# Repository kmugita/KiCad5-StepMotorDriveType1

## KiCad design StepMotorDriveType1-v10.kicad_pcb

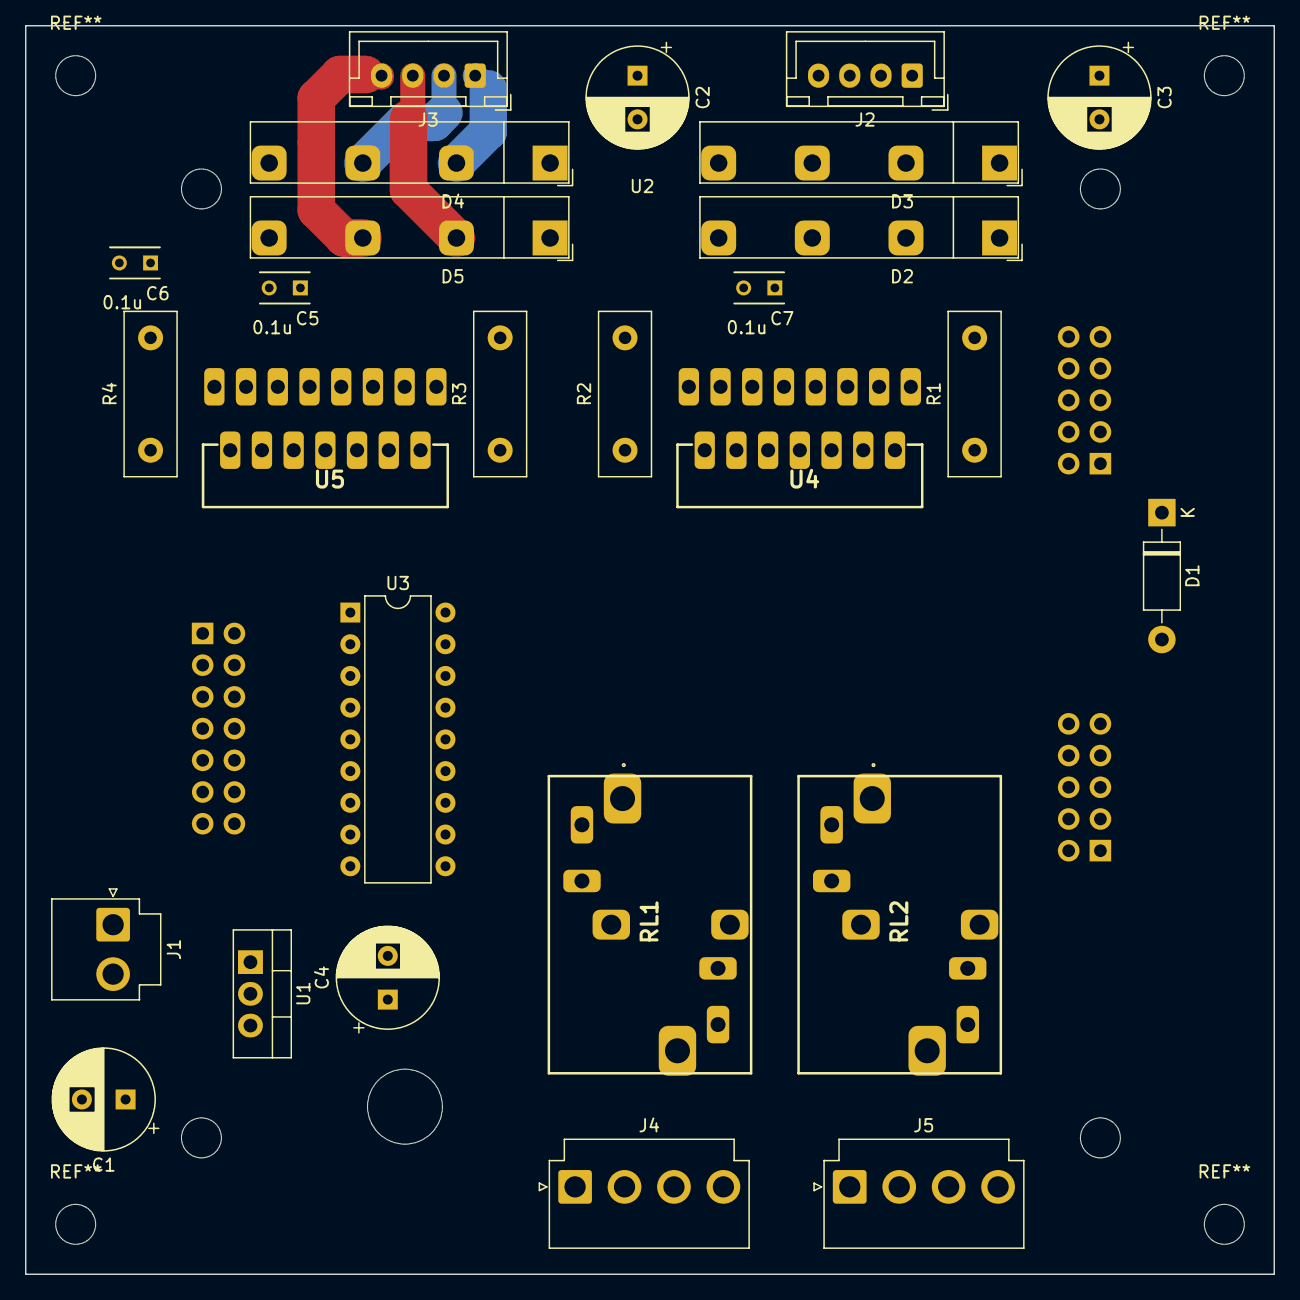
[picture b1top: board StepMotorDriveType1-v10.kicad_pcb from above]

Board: 2 copper layers, 100.0 x 100.0 mm, 28 parts (0 on the bottom side), 47 nets.

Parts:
C1, C2, C3, C4: 220u; CP_Radial_D8.0mm_P3.50mm
C5, C6, C7: 0.1u; C_Ceramic_P2.5
D1: 1N4004; D_DO-41_SOD81_P10.16mm_Horizontal
D2, D3, D4, D5: RBA-406B; Diode_Bridge_RBA-406B
J1: B2P-VH
J2, J3: B4B-XH
J4, J5: B4P-VH
R1, R2, R3, R4: R; R_Box_L13.0mm_W4.0mm_P9.00mm
RL1, RL2: EP2-3L3SAb; EP2_H-BRIDGE
U1: L7805CV-DG; TO-220-3_Vertical
U2: PIC18F45K22-CPUBRD-V2; Pic18f45k22cpubrd
U3: TD62083; DIP-18_W7.62mm
U4, U5: L298N; Multiwatt15_V

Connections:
+5V: C4.1, C5.1, C6.1, C7.1, D1.2, U1.3, U4.9, U5.9
+12V: C1.1, C2.1, C3.1, D2.1, D3.1, D4.1, D5.1, J1.1, RL1.3, RL1.7, RL2.3, RL2.7, U1.1, U3.10
+BATT: U4.4, U5.4
/OUT1: U2.26, U3.1
/OUT2: U2.27, U3.2
/OUT3: U2.28, U3.3
/OUT4: U2.29, U3.4
/OUT5: U2.30, U3.5
/OUT6: U2.31, U3.6
/OUT7: U2.32, U3.7
/OUT8: U2.33, U3.8
DOUT1: RL1.6, U3.18
DOUT2: RL1.2, U3.17
DOUT3: RL2.6, U3.16
DOUT4: RL2.2, U3.15
ENABLE-1: U2.3, U4.6, U4.11
ENABLE-2: U2.4, U5.6, U5.11
GND: C1.2, C2.2, C3.2, C4.2, C5.2, C6.2, C7.2, D2.4, D3.4, D4.4, D5.4, J1.2, R1.1, R2.1, R3.1, R4.1, U1.2, U2.10, U2.20, U2.34, U3.9, U4.8, U5.8
INPUT_1-1: U2.19, U4.5
INPUT_1-2: U2.15, U5.5
INPUT_2-1: U2.18, U4.7
INPUT_2-2: U2.14, U5.7
INPUT_3-1: U2.17, U4.10
INPUT_3-2: U2.13, U5.10
INPUT_4-1: U2.16, U4.12
INPUT_4-2: U2.12, U5.12
unnamed: D1.1, U2.1
unnamed: D2.2, J2.1, U4.2
unnamed: D2.3, J2.2, U4.3
unnamed: D3.2, J2.3, U4.13
unnamed: D3.3, J2.4, U4.14
unnamed: D4.2, J3.1, U5.2
unnamed: D4.3, J3.2, U5.3
unnamed: D5.2, J3.3, U5.13
unnamed: D5.3, J3.4, U5.14
unnamed: J4.1, RL1.4
unnamed: J4.2, RL1.8
unnamed: J4.3, RL1.1
unnamed: J4.4, RL1.5
unnamed: J5.1, RL2.4
unnamed: J5.2, RL2.8
unnamed: J5.3, RL2.1
unnamed: J5.4, RL2.5
unnamed: R1.2, U4.1
unnamed: R2.2, U4.15
unnamed: R3.2, U5.1
unnamed: R4.2, U5.15

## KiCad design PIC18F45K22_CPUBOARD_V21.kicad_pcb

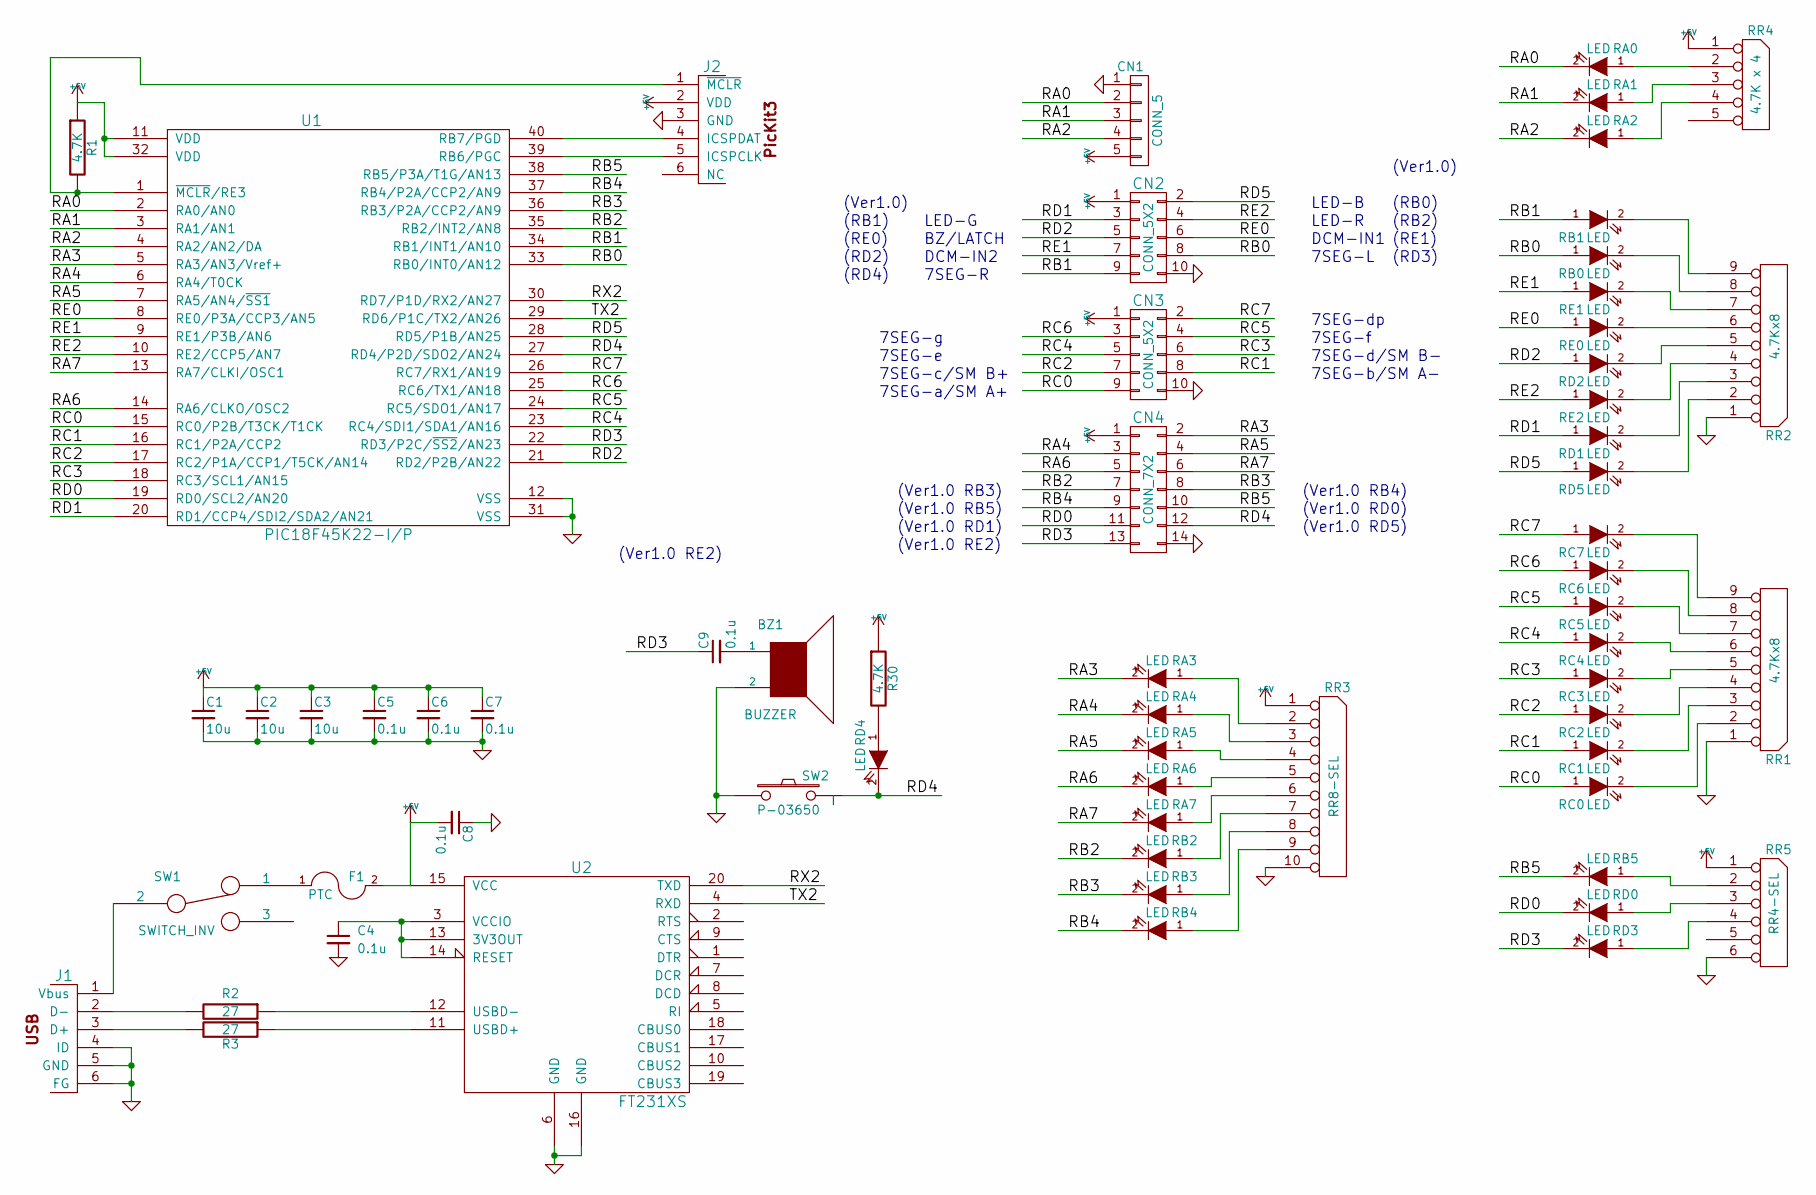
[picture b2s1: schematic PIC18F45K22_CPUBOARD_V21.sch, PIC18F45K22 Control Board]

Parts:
BZ1: BUZZER; Buzzer_12x6.9_Pitch5
C1, C2, C3: 10u; C_Ceramic_P5
C4, C8: 0.1u; C_0603_HandSoldering
C5, C6, C7, C9: 0.1u; C_Ceramic_P2.5
CN1: CONN_5; JST_EH_B05B-EH-A_05x2.50mm_Straight
CN2, CN3: CONN_5X2; IDC_Header_Straight_10pins
CN4: CONN_7X2; IDC_Header_Straight_14pins
F1: PTC; PTC_RXEF050
J1: USB_MiniB; USB_Mini-B_MUSB-5BF01AS
J2: con_PicKit3; Pin_Header_Angled_1x06_R
R1, R30: 4.7K; Resistor_Vertical_RM2.5mm
R2, R3: 27; R_0603_HandSoldering
RA0, RA1, RA2, RA3, RA4, RA5, RA6, RA7: LED; LED-3-S
RB0, RB1, RB2, RB3, RB4, RB5: LED; LED-3-S
RC0, RC1, RC2, RC3, RC4, RC5, RC6, RC7: LED; LED-3-S
RD0, RD1, RD2, RD3, RD4, RD5: LED; LED-3-S
RE0, RE1, RE2: LED; LED-3-S
RR1, RR2: 4.7Kx8; Resistor_Array_SIP8
RR3: RR8-SEL; Resistor_Array_SIP8-SEL
RR4: 4.7K x 4; Resistor_Array_SIP4
RR5: RR4-SEL; Resistor_Array_SIP4-SEL
SW1: SWITCH_INV; SW_2MS1-T1-B4-M2
SW2: P-03650; SW_TH_Tactile_P-036xx
U1: PIC18F45K22-I/P; DIP-40_W15.24mm_LongPads_withSocket
U2: FT231XS; SSOP-20_4.4x8.6mm_Pitch0.635mm

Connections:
+5V: C1.1, C2.1, C3.1, C5.1, C6.1, C7.1, C8.2, CN1.5, CN2.1, CN3.1, CN4.1, F1.2, J2.2 (VDD), R1.1, R30.1, RR3.1 (V-COM), RR4.1 (COM), RR5.1 (VCC-COM), U1.11 (VDD), U1.32 (VDD), U2.15 (VCC)
/RA0: CN1.2, RA0.2 (K), U1.2 (RA0/AN0)
/RA1: CN1.3, RA1.2 (K), U1.3 (RA1/AN1)
/RA2: CN1.4, RA2.2 (K), U1.4 (RA2/AN2/DA)
/RA3: CN4.2, RA3.2 (K), U1.5 (RA3/AN3/Vref+)
/RA4: CN4.3, RA4.2 (K), U1.6 (RA4/T0CK)
/RA5: CN4.4, RA5.2 (K), U1.7 (RA5/AN4/~SS1~)
/RA6: CN4.5, RA6.2 (K), U1.14 (RA6/CLKO/OSC2)
/RA7: CN4.6, RA7.2 (K), U1.13 (RA7/CLKI/OSC1)
/RB0: CN2.8, RB0.1 (A), U1.33 (RB0/INT0/AN12)
/RB1: CN2.9, RB1.1 (A), U1.34 (RB1/INT1/AN10)
/RB2: CN4.7, RB2.2 (K), U1.35 (RB2/INT2/AN8)
/RB3: CN4.8, RB3.2 (K), U1.36 (RB3/P2A/CCP2/AN9)
/RB4: CN4.9, RB4.2 (K), U1.37 (RB4/P2A/CCP2/AN9)
/RB5: CN4.10, RB5.2 (K), U1.38 (RB5/P3A/T1G/AN13)
/RC0: CN3.9, RC0.1 (A), U1.15 (RC0/P2B/T3CK/T1CK)
/RC1: CN3.8, RC1.1 (A), U1.16 (RC1/P2A/CCP2)
/RC2: CN3.7, RC2.1 (A), U1.17 (RC2/P1A/CCP1/T5CK/AN14)
/RC3: CN3.6, RC3.1 (A), U1.18 (RC3/SCL1/AN15)
/RC4: CN3.5, RC4.1 (A), U1.23 (RC4/SDI1/SDA1/AN16)
/RC5: CN3.4, RC5.1 (A), U1.24 (RC5/SDO1/AN17)
/RC6: CN3.3, RC6.1 (A), U1.25 (RC6/TX1/AN18)
/RC7: CN3.2, RC7.1 (A), U1.26 (RC7/RX1/AN19)
/RD0: CN4.11, RD0.2 (K), U1.19 (RD0/SCL2/AN20)
/RD1: CN2.3, RD1.1 (A), U1.20 (RD1/CCP4/SDI2/SDA2/AN21)
/RD2: CN2.5, RD2.1 (A), U1.21 (RD2/P2B/AN22)
/RD3: C9.1, CN4.13, RD3.2 (K), U1.22 (RD3/P2C/~SS2~/AN23)
/RD4: CN4.12, RD4.2 (K), SW2.3, U1.27 (RD4/P2D/SDO2/AN24)
/RD5: CN2.2, RD5.1 (A), U1.28 (RD5/P1B/AN25)
/RE0: CN2.6, RE0.1 (A), U1.8 (RE0/P3A/CCP3/AN5)
/RE1: CN2.7, RE1.1 (A), U1.9 (RE1/P3B/AN6)
/RE2: CN2.4, RE2.1 (A), U1.10 (RE2/CCP5/AN7)
/RX2: U1.30 (RD7/P1D/RX2/AN27), U2.20 (TXD)
/TX2: U1.29 (RD6/P1C/TX2/AN26), U2.4 (RXD)
GND: BZ1.2, C1.2, C2.2, C3.2, C4.2, C5.2, C6.2, C7.2, C8.1, CN1.1, CN2.10, CN3.10, CN4.14, J1.4 (ID), J1.5 (GND), J1.6 (FG), J2.3 (GND), RR1.1 (COM), RR2.1 (COM), RR3.10 (G-COM), RR5.6 (GND-COM), SW2.1, U1.12 (VSS), U1.31 (VSS), U2.6 (GND), U2.16 (GND)
unnamed: BZ1.1, C9.2
unnamed: C4.1, U2.3 (VCCIO), U2.13 (3V3OUT), U2.14 (RESET)
unnamed: F1.1, SW1.1
unnamed: J1.1 (Vbus), SW1.2
unnamed: J1.2 (D-), R2.2
unnamed: J1.3 (D+), R3.2
unnamed: J2.1 (~MCLR~), R1.2, U1.1 (~MCLR~/RE3)
unnamed: J2.4 (ICSPDAT), U1.40 (RB7/PGD)
unnamed: J2.5 (ICSPCLK), U1.39 (RB6/PGC)
unnamed: R2.1, U2.12 (USBD-)
unnamed: R3.1, U2.11 (USBD+)
unnamed: R30.2, RD4.1 (A)
unnamed: RA0.1 (A), RR4.2
unnamed: RA1.1 (A), RR4.3
unnamed: RA2.1 (A), RR4.4
unnamed: RA3.1 (A), RR3.2
unnamed: RA4.1 (A), RR3.3
unnamed: RA5.1 (A), RR3.4
unnamed: RA6.1 (A), RR3.5
unnamed: RA7.1 (A), RR3.6
unnamed: RB0.2 (K), RR2.8
unnamed: RB1.2 (K), RR2.9
unnamed: RB2.1 (A), RR3.7
unnamed: RB3.1 (A), RR3.8
unnamed: RB4.1 (A), RR3.9
unnamed: RB5.1 (A), RR5.2
unnamed: RC0.2 (K), RR1.2
unnamed: RC1.2 (K), RR1.3
unnamed: RC2.2 (K), RR1.4
unnamed: RC3.2 (K), RR1.5
unnamed: RC4.2 (K), RR1.6
unnamed: RC5.2 (K), RR1.7
unnamed: RC6.2 (K), RR1.8
unnamed: RC7.2 (K), RR1.9
unnamed: RD0.1 (A), RR5.3
unnamed: RD1.2 (K), RR2.3
unnamed: RD2.2 (K), RR2.5
unnamed: RD3.1 (A), RR5.4
unnamed: RD5.2 (K), RR2.2
unnamed: RE0.2 (K), RR2.6
unnamed: RE1.2 (K), RR2.7
unnamed: RE2.2 (K), RR2.4

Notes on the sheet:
LED-B
LED-G
LED-R
BZ/LATCH
DCM-IN1
DCM-IN2
7SEG-L
7SEG-R
(RB0)
(RB2)
(RE1)
(RD3)
(RB1)
(RE0)
(RD2)
(RD4)
(Ver1.0)
(Ver1.0 RE2)
(Ver1.0 RD1)
(Ver1.0 RD5)
(Ver1.0 RD0)
(Ver1.0 RB4)
(Ver1.0 RB3)
(Ver1.0 RB5)
7SEG-dp
7SEG-g
7SEG-f
7SEG-e
7SEG-c/SM B+
7SEG-d/SM B-
7SEG-b/SM A-
7SEG-a/SM A+

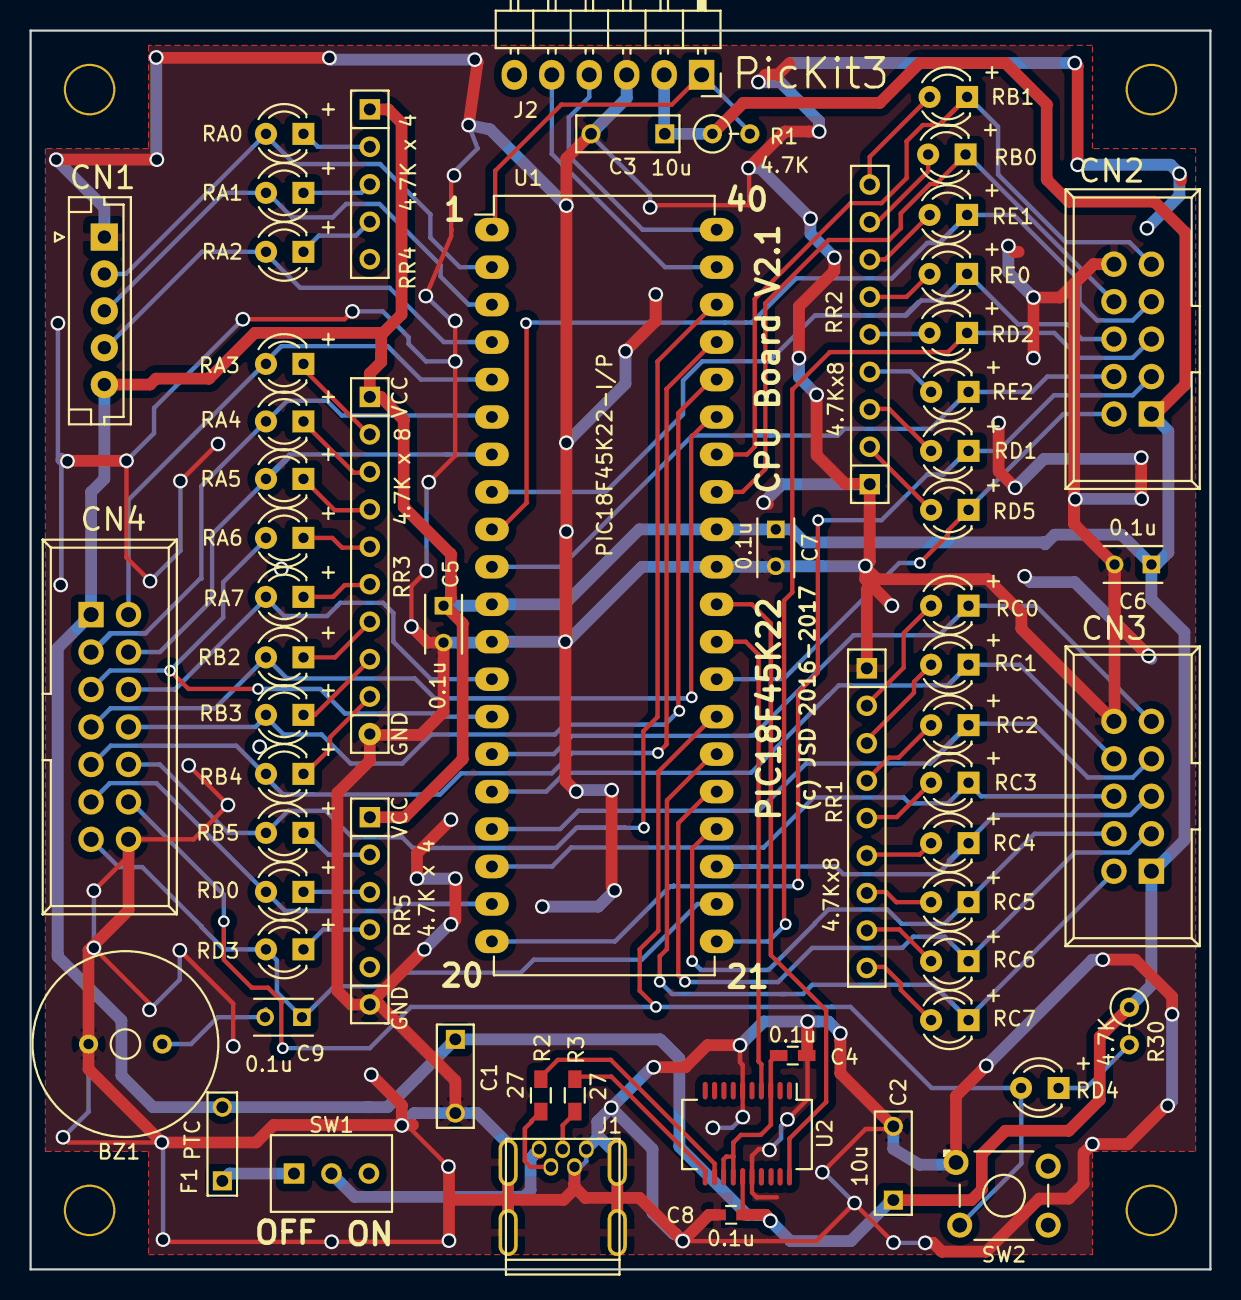
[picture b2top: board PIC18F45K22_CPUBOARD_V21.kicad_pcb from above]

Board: 2 copper layers, 80.0 x 84.0 mm, 61 parts (0 on the bottom side), 77 nets.

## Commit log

2019-04-27 PIC18F45K22 CPUBOARD for KiCad v5
2019-04-29 modify 20190429
2019-05-09 Step Motor Driver for KiCad5
